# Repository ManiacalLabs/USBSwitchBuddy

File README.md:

# USB Switch Buddy

The USB Switch Buddy was made to solve a simple problem: Connecting to a USB device without also powering it off the USB host.

Originally this came about with one of our 3D printers where the main control board would receive power from the Raspberry Pi running OctoPrint. The original solution was some mild surgery on a spare USB cable. But there are plenty of other situations we run into on a regular basis where this has become a problem. For example, many of our LED displays require far more power than USB can deliver, so power is provided to the micro-controller separate from the USB connection. With the USB Switch Buddy that's no longer a problem.

We considered not including a switch at all. But decided that it could come in handy, allowing you to power cycle a USB device without fully unplugging the cable. To top it all off, there's a 4-pin 0.1" header allowing you to monitor the USB line voltage and even the data lines, should you need to.

# Bill Of Materials

- [PCB](https://oshpark.com/shared_projects/nIXL0D1j)
- [Male USB Connector](https://www.mouser.com/ProductDetail/490-UP2-AH-1-TH)
- [Female USB Connector](https://www.mouser.com/ProductDetail/490-UJ2-AH-4-TH)
- [Switch](https://www.mouser.com/ProductDetail/611-JS202011CQN)

# Assembly

As there are only 4 components, including the PCB, assembly is pretty easy even for the most novice soldering skills.

**Note:** *Before beginning check if there are any small protrusions on the edge of the PCB for the male USB connector. These are a natural part of the PCB manufacturing process but in the case of the male USB connector it may need to be lightly sanded down so that edge is entirely flush.*

First connect the male USB connector where labeled. Put the connector in place and flip the board over. We've found that placing the switch on its side under the female side of the PCB is a perfect way to hold the PCB in the correct position.

Solder just one of 4 main pins and check that the connector is still flush and parallel to the PCB, like so:

Then solder the other 3 connector pins. Then solder the 2 larger posts, being sure to flow solder fully into the post holes for a strong mechanical connection.

Next, do the same with the female USB connector, soldering just one pin first:

Verify that the connector is straight and flush and, once it is, repeat the steps with all connector pins and the 2 larger posts.

Finally, if you want it, insert the switch (direction does not matter) and hold it in place with a small piece of tape. Then solder all 6 pins.

That's it! You are ready to go!

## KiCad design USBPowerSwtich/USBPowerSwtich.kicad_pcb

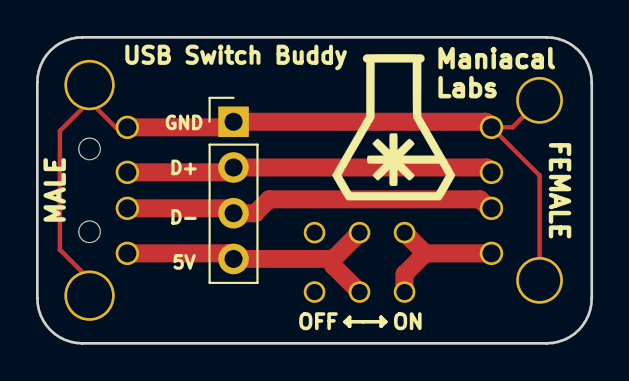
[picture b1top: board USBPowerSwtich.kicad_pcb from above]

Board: 2 copper layers, 30.8 x 17.0 mm, 4 parts (0 on the bottom side), 5 nets.

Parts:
J1: USB_A_Male; UP2-AH-1-TH
J2: USB_A_Female; UJ2-AH-4-TH
J3: Test; Socket_Strip_Straight_1x04_Pitch2.54mm
SW1: Power; JS202011CQN

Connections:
GND: J1.4, J1.5, J2.4, J2.5, J3.1
unnamed: J1.2, J2.2, J3.3
unnamed: J1.3, J2.3, J3.2
unnamed: J2.1, SW1.3
VCC: J1.1, J3.4, SW1.2

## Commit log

2018-09-16 Updating silkscreen and outline
2018-09-16 Added name
2018-09-16 Moving silk screen layout
2018-10-08 Tweak switch placement
2018-10-22 Changing name
2018-10-23 Adding doc
2018-10-23 Adding license
2018-10-23 fix typos
2018-10-23 fix typo
